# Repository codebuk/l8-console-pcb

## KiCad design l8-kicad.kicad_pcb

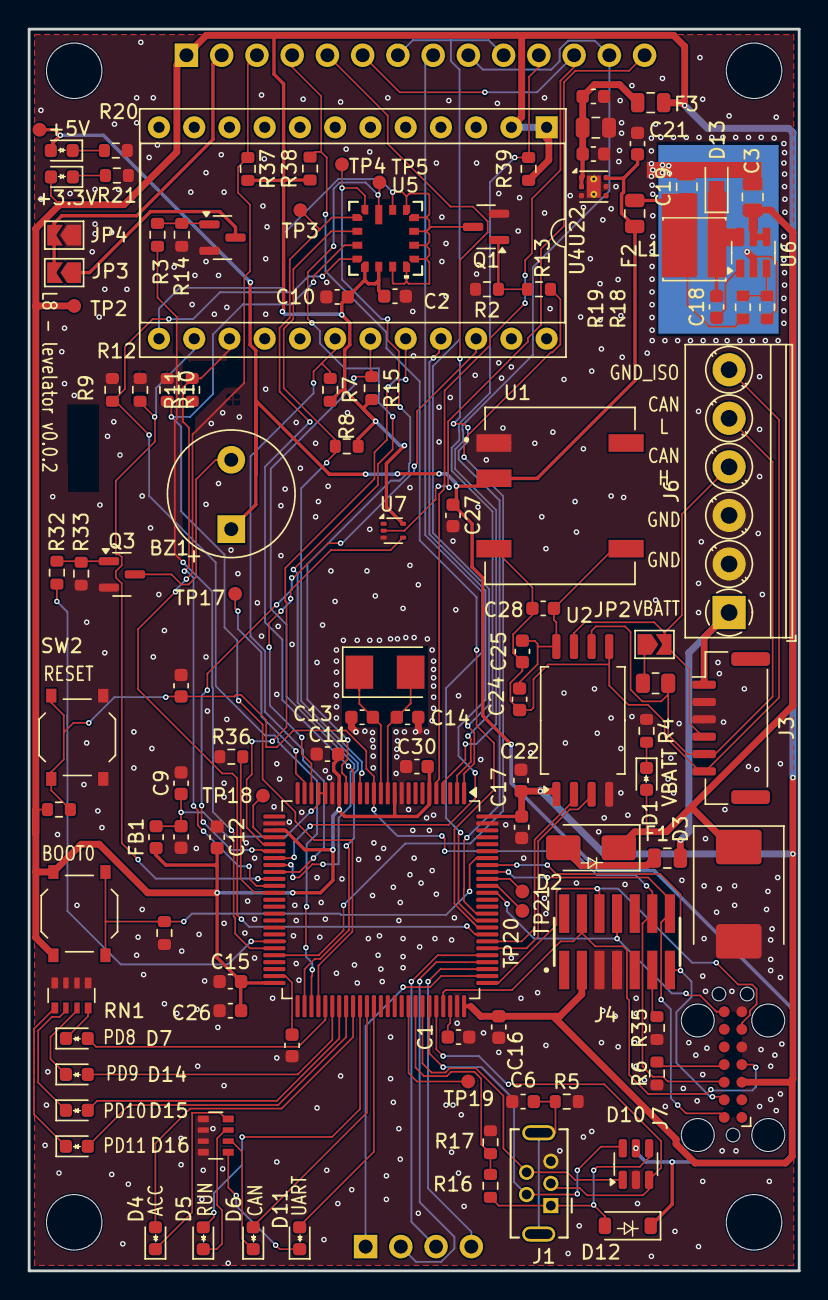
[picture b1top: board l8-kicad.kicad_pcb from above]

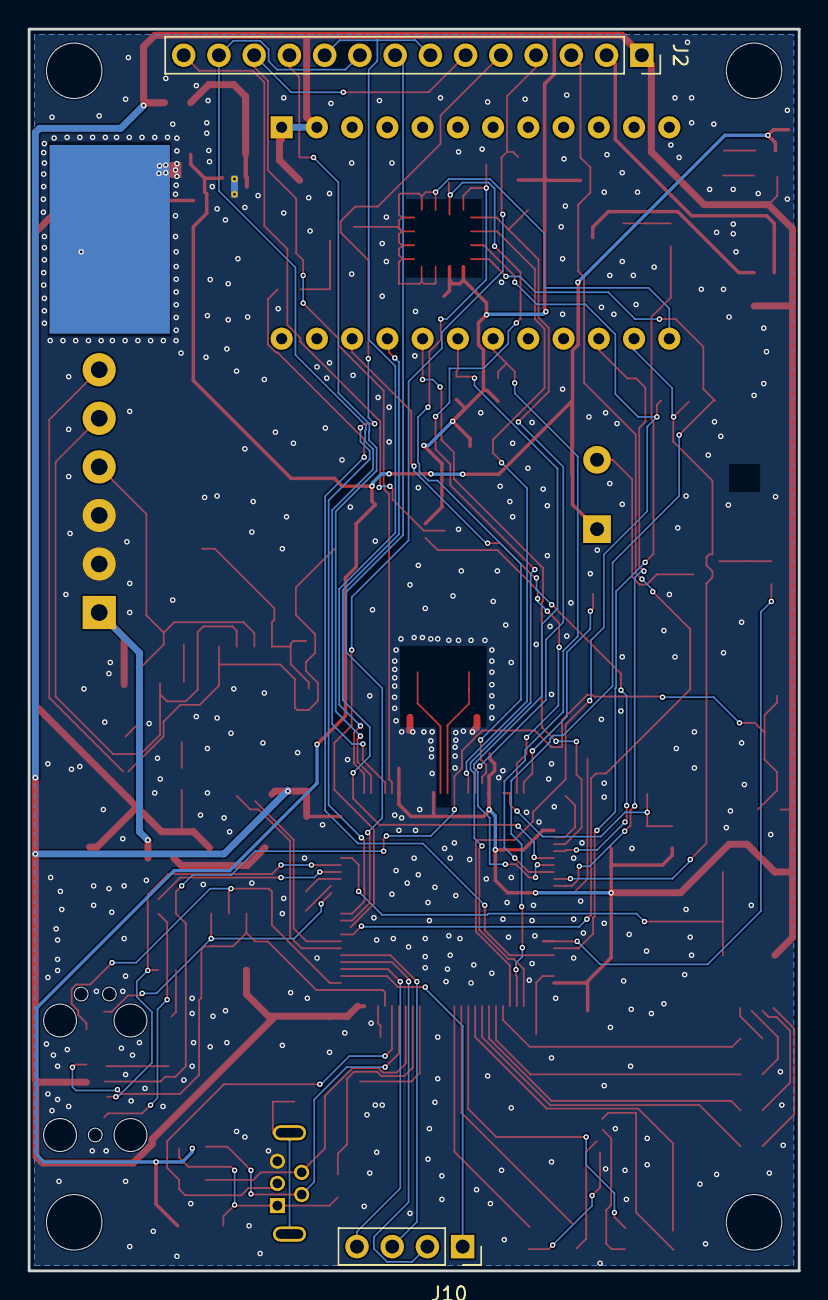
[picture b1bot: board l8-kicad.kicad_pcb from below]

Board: 2 copper layers, 55.5 x 89.5 mm, 121 parts (2 on the bottom side), 100 nets.

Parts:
BZ1: Buzzer; Buzzer_9x9.5RM5.0
C1, C8: 2.2uF; C_0603_1608Metric
C2, C4, C6, C9, C11, C12, C15, C16, C17, C18, C22, C25, C30: 100nF; C_0603_1608Metric
C3: 10uF; C_0805_2012Metric
C5, C23: 1uF; C_0603_1608Metric
C7, C19: 22uF; C_0805_2012Metric
C10, C21, C24, C26, C27, C28: 10uF; C_0603_1608Metric
C13, C14: 18pF; C_0603_1608Metric
C20: 10nF; C_0603_1608Metric
D1, D6, D8, D9, D15: LED-RED; LED_0603_1608Metric - polarity
D2: SS54; D_SMA - polarity
D3: SM15T100CA; D_SMC
D4, D7, D11, D16: LED-YELLOW; LED_0603_1608Metric - polarity
D5, D14: LED-WHITE; LED_0603_1608Metric - polarity
D10: SRV05-4; SOT-23-6
D12: B5819W; D_SOD-123-polarity
D13: MicroSMP(DO-219AD); D_MicroSMP_AK
F1, F2, F3: Fuse; Fuse_0805_2012Metric
FB1: 4.7uH; L_0603_1608Metric
H1, H2, H3, H4: MountingHole; MountingHole_4mm
J1: USB_B_Mini; USB-MINI-B-VERTICAL
J2: LCD 3.2" 240x320 Conn_01x14_Pin; PinSocket_1x14_P2.54mm_Vertical
J3: JST GH; JST_GH_BM06B-GHS-TBT_1x06-1MP_P1.25mm_Vertical
J4: Conn_ST_STDC14; SAMTEC_FTSH-107-01-F-DV-K-Fix
J6: Screw_Terminal_01x06; TerminalBlock_Phoenix_PT-1,5-6-3.5-H_1x06_P3.50mm_Horizontal
J7: TC2070 - TAG Connect; Tag-Connect_TC2070-IDC-FP_2x07_P1.27mm_Vertical
J10: Conn_01x04_Pin; PinSocket_1x04_P2.54mm_Vertical
JP2, JP4: SolderJumper_2_Bridged; SolderJumper-2_P1.3mm_Open_TrianglePad1.0x1.5mm
JP3: SolderJumper_2_Open; SolderJumper-2_P1.3mm_Open_TrianglePad1.0x1.5mm
L1: 3.3uH; L_Sunlord_SWPA4030S
Q1, Q2, Q3: AO3400A; SOT-23
R1: 120R; R_0805_2012Metric
R2, R7, R8, R9, R10, R11, R12, R14, R15, R16, R18, R33, R36, R37, R38, R39, R43, R45: 10K; R_0603_1608Metric
R3, R6, R13, R32, R35: 100R; R_0603_1608Metric
R4, R17, R20, R21: 2.2K; R_0603_1608Metric
R5: 100K; R_0603_1608Metric
R19: 54K9; R_0603_1608Metric
RN1, RN2: 1k; R_Array_Convex_4x0603
SW1, SW2: SW_Push; SW_Push_1P1T_XKB_TS-1187A
TP1: 5V; TestPoint_Pad_D1.0mm FP .6R
TP2: +3.3V; TestPoint_Pad_D1.0mm FP .6R
TP3, TP4: IIS3DHHCTR_SDI; TestPoint_Pad_D1.0mm FP .6R
TP5: IIS3DHHCTR_SCK; TestPoint_Pad_D1.0mm FP .6R
TP17: PA1; TestPoint_Pad_D1.0mm FP .6R
TP18: PA4; TestPoint_Pad_D1.0mm FP .6R
TP19: PA8; TestPoint_Pad_D1.0mm FP .6R
TP20: PB4; TestPoint_Pad_D1.0mm FP .6R
TP21: PB5; TestPoint_Pad_D1.0mm FP .6R
U1: B0505XT-1WR3; 0505_Isolated_SMD
U2: ISO1042-Q1; SOIC-8_7.5x5.85mm_P1.27mm
U3: STM32F427V_G-I_Tx; LQFP-100_14x14mm_P0.5mm
U4: ST_SENSOR_2; DIP-24_W15.24mm_Socket- nox
U5: IIS3DHHCTR; CCLGA-16L_5X5X1P7_STM
U6: LMR14006YDDCR; SOT-23-6
U7: SN74LVC1G14DRLR; SOT-553
U22: TLV76733DRVx; WSON-6-1EP_2x2mm_P0.65mm_EP1x1.6mm_ThermalVias
X1: 8MHz 20pF; Crystal_SMD_5032-2Pin_5.0x3.2mm

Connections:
+3.3VP: C2.1, C10.1, C11.2, C12.2, C15.2, C16.2, C17.2, C22.1, C26.2, C30.2, D9.2 (A), F3.2, FB1.1, J2.1 (VCC), J4.3 (VCC), J7.3 (VCC), R7.2, R8.2, R15.2, R37.2, R38.2, R39.2, R43.1, SW1.1, TP2.1, U2.1 (VCC1), U3.6 (VBAT), U3.11 (VDD), U3.19 (VDD), U3.28 (VDD), U3.50 (VDD), U3.75 (VDD), U3.100 (VDD), U4.1 (VDD), U4.2 (VDD_IO), U5.7 (VDD_IO), U5.8 (VDD), U7.5 (VCC)
+5V: BZ1.1 (+), C21.1, C27.1, D8.2 (A), D10.5, D12.1 (K), F2.2, TP1.1, U1.2 (+VIN), U22.6 (IN)
/+5V_ISO: C24.1, C25.1, C28.1, U1.5 (+VOUT), U2.8 (VCC2)
/CAN1_RX: U2.3 (RXD), U3.81 (PD0)
/CAN1_TX: U2.2 (TXD), U3.82 (PD1)
/GND_ISO: C24.2, C25.2, C28.2, J3.6, J6.6, U1.4 (-VOUT), U2.5 (GND2)
/LCD_DC: J2.5 (D/C), U3.86 (PD5)
/LCD_LED: J2.8 (LED), U3.85 (PD4)
/LCD_ON: R3.2, U3.45 (PE14)
/LCD_RESET: J2.4 (RESET), R38.1, U3.84 (PD3)
/MCU/BEEPER: R32.2, U3.44 (PE13)
/MCU/BOOT0: R45.2, SW1.2, U3.94 (BOOT0)
/MCU/BOOT1: R36.2, U3.37 (PB2)
/MCU/NRST: C20.2, J4.12 (~RST), J7.12 (~RST), R43.2, SW2.1, U3.14 (NRST)
/MCU/PA1: TP17.1, U3.24 (PA1)
/MCU/PA4: TP18.1, U3.29 (PA4)
/MCU/PA8: TP19.1, U3.67 (PA8)
/MCU/PB4: TP20.1, U3.90 (PB4)
/MCU/PB5: TP21.1, U3.91 (PB5)
/MCU/PD8: D7.2 (A), U3.55 (PD8)
/MCU/PD9: D14.2 (A), U3.56 (PD9)
/MCU/PD10: D15.2 (A), U3.57 (PD10)
/MCU/PD11: D16.2 (A), U3.58 (PD11)
/MCU/PD12: D4.2 (A), U3.59 (PD12)
/MCU/PD13: D5.2 (A), U3.60 (PD13)
/MCU/PD14: D6.2 (A), U3.61 (PD14)
/MCU/PD15: D11.2 (A), U3.62 (PD15)
/MCU/RCC_OSC_IN: C13.1, U3.12 (PH0), X1.2
/MCU/RCC_OSC_OUT: C14.1, U3.13 (PH1), X1.1
/MCU/SYS_JTCK-SWCLK: J4.6 (JCLK/SWCLK), J7.6 (JCLK/SWCLK), U3.76 (SYS_JTCK-SWCLK)
/MCU/SYS_JTDO-SWO: J4.8 (JTDO/SWO), J7.8 (JTDO/SWO), U3.89 (SYS_JTDO-SWO)
/MCU/SYS_JTMS-SWDIO: J4.4 (JTMS/SWDIO), J7.4 (JTMS/SWDIO), U3.72 (SYS_JTMS-SWDIO)
/MCU/USART1_RX: J4.13 (VCP_RX), J7.13 (VCP_RX), U3.93 (USART1_RX)
/MCU/USART1_TX: J4.14 (VCP_TX), J7.14 (VCP_TX), U3.92 (USART1_TX)
/PA10: D10.1, J1.4 (ID), U3.69 (PA10)
/SENSOR_ON: R13.1, U3.46 (PE15)
/SPI1_CS: R15.1, U3.33 (PC4), U4.19 (CS)
/SPI1_CS2: R7.1, U3.34 (PC5), U4.18 (SPI_dut_CS2)
/SPI1_IRQ: R12.2, U3.35 (PB0), U4.14 (DIL_INT1)
/SPI1_IRQ2: R11.2, U3.36 (PB1), U4.15 (DIL_INT2)
/SPI1_SCK: U3.30 (SPI1_SCK), U4.20 (SCL)
/SPI1_SDI: U3.31 (SPI1_MISO), U4.22 (SDO)
/SPI1_SDO: U3.32 (SPI1_MOSI), U4.21 (SDA)
/SPI2_CS: R8.1, U3.16 (PC1), U5.4 (CS)
/SPI2_IRQ: R9.2, U3.53 (PB14), U5.6 (INT1)
/SPI2_IRQ2: R10.2, U3.54 (PB15), U5.5 (INT2)
/SPI2_SCK: TP5.1, U3.52 (SPI2_SCK), U5.1 (SPC)
/SPI2_SDI: TP3.1, U3.17 (SPI2_MISO), U5.3 (SDO)
/SPI2_SDO: TP4.1, U3.18 (SPI2_MOSI), U5.2 (SDI)
/SPI3_CS: J10.1, U3.77 (PA15)
/SPI3_SCK: J10.4, U3.78 (SPI3_SCK)
/SPI3_SDI: J10.2, U3.79 (SPI3_MISO)
/SPI3_SDO: J10.3, U3.80 (SPI3_MOSI)
/SPI4_CS_1: J2.11 (T_CS), R39.1, U3.2 (PE3)
/SPI4_CS_2: J2.3 (CS), R37.1, U3.83 (PD2)
/SPI4_SCK: J2.7 (SCK), J2.10 (T_SCK), U3.1 (SPI4_SCK)
/SPI4_SDI: J2.9 (SDO), J2.13 (T_SDO), U3.4 (SPI4_MISO)
/SPI4_SDO: J2.6 (SDI), J2.12 (T_SDI), U3.5 (SPI4_MOSI)
/SYS_WAKEUP: U3.23 (SYS_WKUP), U7.4
/USB_OTG_FS_DM: D10.6, J1.2 (D-), U3.70 (USB_OTG_FS_DM)
/USB_OTG_FS_DP: D10.3, J1.3 (D+), U3.71 (USB_OTG_FS_DP)
/USB_OTG_FS_VBUS: R16.2, R17.2, U3.68 (USB_OTG_FS_VBUS)
/VBATT: F1.1, J3.1, J6.1
/can/CAN_H: J3.4, J6.4, JP2.2 (B), U2.7 (CANH)
/can/CAN_L: J3.5, J6.5, R1.1, U2.6 (CANL)
/usb/Shield: C6.1, J1.6 (Shield), R5.1
GND: C1.2, C2.2, C3.2, C4.2, C5.1, C6.2, C7.2, C8.2, C9.2, C10.2, C11.1, C12.1, C13.2, C14.2, C15.1, C16.1, C17.1, C19.2, C20.1, C21.2, C22.2, C23.1, C26.1, C27.2, C30.1, D3.2 (A2), D10.2, D13.2 (A), J1.5 (GND), J3.2, J3.3, J4.5 (GND), J4.7 (GND), J6.2, J6.3, J7.5 (GND), J7.7 (GND), JP4.1 (A), Q1.2 (S), Q2.2 (S), Q3.2 (S), R2.1, R4.1, R5.2, R6.2, R9.1, R10.1, R11.1, R12.1, R14.1, R17.1, R18.1, R20.1, R21.1, R33.1, R35.2, R36.1, R45.1, RN1.5 (R4.2), RN1.6 (R3.2), RN1.7 (R2.2), RN1.8 (R1.2), RN2.5 (R4.2), RN2.6 (R3.2), RN2.7 (R2.2), RN2.8 (R1.2), SW2.2, U1.1 (-VIN), U2.4 (GND1), U3.10 (VSS), U3.20 (VSSA), U3.27 (VSS), U3.74 (VSS), U3.99 (VSS), U6.2 (GND), U7.3 (GND), U22.3 (GND), U22.5 (GND), U22.7 (PAD)
unnamed: BZ1.2 (-), Q3.3 (D)
unnamed: C19.1, F2.1, L1.2, R19.1
unnamed: C3.1, D1.2 (A), D2.1 (K), D3.1 (A1), U6.4 (~SHDN), U6.5 (VIN)
unnamed: D1.1 (K), R4.2
unnamed: D2.2 (A), F1.2
unnamed: D4.1 (K), RN2.4 (R4.1)
unnamed: D5.1 (K), RN2.3 (R3.1)
unnamed: D6.1 (K), RN2.2 (R2.1)
unnamed: D7.1 (K), RN1.4 (R4.1)
unnamed: D8.1 (K), R20.2
unnamed: D9.1 (K), R21.2
unnamed: D11.1 (K), RN2.1 (R1.1)
unnamed: D10.4, D12.2 (A), J1.1 (VBUS), R16.1
unnamed: C18.2, D13.1 (K), L1.1, U6.6 (SW)
unnamed: D14.1 (K), RN1.3 (R3.1)
unnamed: D15.1 (K), RN1.2 (R2.1)
unnamed: D16.1 (K), RN1.1 (R1.1)
unnamed: J2.2 (GND), JP3.2 (B), JP4.2 (B)
unnamed: J2.14 (T_IRQ), U7.2
unnamed: J4.11 (GNDDetect), R35.1
unnamed: J7.11 (GNDDetect), R6.1
unnamed: JP2.1 (A), R1.2
unnamed: JP3.1 (A), Q2.3 (D)
unnamed: Q1.3 (D), U4.13 (GND), U5.9 (GND), U5.10 (GND__1), U5.11 (GND__2), U5.12 (GND__3), U5.13 (GND__4), U5.14 (GND__5), U5.15 (GND__6), U5.16 (GND__7)
unnamed: Q1.1 (G), R2.2, R13.2
unnamed: Q2.1 (G), R3.1, R14.2
unnamed: Q3.1 (G), R32.1, R33.2
unnamed: C8.1, U3.49 (VCAP_1)
unnamed: C1.1, U3.73 (VCAP_2)
unnamed: C9.1, C23.2, FB1.2, U3.21 (VREF+), U3.22 (VDDA)
unnamed: C18.1, U6.1 (CB)
unnamed: R18.2, R19.2, U6.3 (FB)
unnamed: C4.1, C5.2, C7.1, F3.1, U22.1 (OUT), U22.2 (SNS)

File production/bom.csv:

Designator,Footprint,Quantity,Value,LCSC Part #
BZ1,Buzzer_9x9.5RM5.0,1,Buzzer,C96493
"C1, C8",0603,2,2.2uF,C23630
"C10, C21, C24, C26, C27, C28",0603,6,10uF,C96446
"C11, C12, C15, C16, C17, C18, C2, C22, C25, C30, C4, C6, C9",0603,13,100nF,C14663
"C13, C14",0603,2,18pF,C1647
"C19, C7",0805,2,22uF, C45783
C20,0603,1,10nF,C57112
"C23, C5",0603,2,1uF,C15849
C3,0805,1,10uF,C440198
"D1, D15, D6, D8, D9",0603,5,LED-RED,C2286
D10,SOT-23-6,1,SRV05-4,C2836319
"D11, D16, D4, D7",0603,4,LED-YELLOW,C72038
D12,D_SOD-123-polarity,1,B5819W,C8598
D13,D_MicroSMP_AK,1,MicroSMP(DO-219AD),C3757499
"D14, D5",0603,2,LED-WHITE,C2290
D2,D_SMA - polarity,1,SS54,C22452
D3,D_SMC,1,SM15T100CA,C1975873
"F1, F2, F3",0805,3,Fuse,C2833485
FB1,0603,1,4.7uH,C1034
J10,PinSocket_1x04_P2.54mm_Vertical,1,Conn_01x04_Pin,C7500773
J3,JST_GH_BM06B-GHS-TBT_1x06-1MP_P1.25mm_Vertical,1,JST  GH,C189892
J6,"TerminalBlock_Phoenix_PT-1,5-6-3.5-H_1x06_P3.50mm_Horizontal",1,Screw_Terminal_01x06,C5290323
L1,L_Sunlord_SWPA4030S,1,3.3uH,C15269
"Q1, Q2, Q3",SOT-23,3,AO3400A,
R1,0805,1,120R,C17437
"R10, R11, R12, R14, R15, R16, R18, R2, R33, R36, R37, R38, R39, R43, R45, R7, R8, R9",0603,18,10K,C25804
"R13, R3, R32, R35, R6",0603,5,100R,C22775
"R17, R20, R21, R4",0603,4,2.2K,C4190
R19,0603,1,54K9,C185321
R5,0603,1,100K,C25803
"RN1, RN2",R_Array_Convex_4x0603,2,1k,C20197
"SW1, SW2",SW_Push_1P1T_XKB_TS-1187A,2,SW_Push,C318884
U1,0505_Isolated_SMD,1,B0505XT-1WR3,C19188495
U2,SOIC-8_7.5x5.85mm_P1.27mm,1,ISO1042-Q1,C2672259
U22,WSON-6-1EP_2x2mm_P0.65mm_EP1x1.6mm_ThermalVias,1,TLV76733DRVx,C2848334
U3,LQFP-100_14x14mm_P0.5mm,1,STM32F427V_G-I_Tx,C117815
U6,SOT-23-6,1,LMR14006YDDCR,C477919
U7,SOT-553,1,SN74LVC1G14DRLR,C2877550
X1,Crystal_SMD_5032-2Pin_5.0x3.2mm,1,8MHz 20pF,C115962

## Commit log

2024-05-30 init
2024-05-30 Remove
2024-05-30 change power add buzzer
2024-05-30 remove hellen
2024-05-30 cleanups
2024-05-30 clean
2024-05-30 finalise debug header and test points
2024-05-30 pre quilter
2024-06-02 rearrange for quilter
2024-06-02 Revert "rearrange for quilter"
    This reverts commit 82a1e797225e255e696808b0918d11e4c10e76df.
2024-06-03 changed to tp and subbed to quilter
2024-06-04 pre quilter - actually saved
2024-06-04 fix bogus lib path
2024-06-04 remove tp and rotate cpu
2024-06-05 smaller caps remove ringing resistors
2024-06-05 add tp move leds +
2024-06-05 usb sheet
2024-06-05 smaller test pads
2024-06-06 pre-quilter after cap size issue
2024-06-06 pre-quilter after cap size issue - forgot to save and last commit was forced
2024-06-07 last comment was incorrect - fix 100nf caps pre jlcpcb
2024-06-07 pre JLCPCB try 1
2024-06-07 change to 2.2k for 12v LED
2024-06-07 STM32 C117815
2024-06-07 SENT TO jlcpcb
2024-07-18 version 2 changes
2024-07-18 close kicad
2024-07-19 5v buck
2024-09-17 version 2 initial
2024-09-17 version 2 initial- fixes
2025-04-07 appears to be final on old fedora - correct orient c30 and gnd planes
2025-04-07 update to version 9 on selwyn
